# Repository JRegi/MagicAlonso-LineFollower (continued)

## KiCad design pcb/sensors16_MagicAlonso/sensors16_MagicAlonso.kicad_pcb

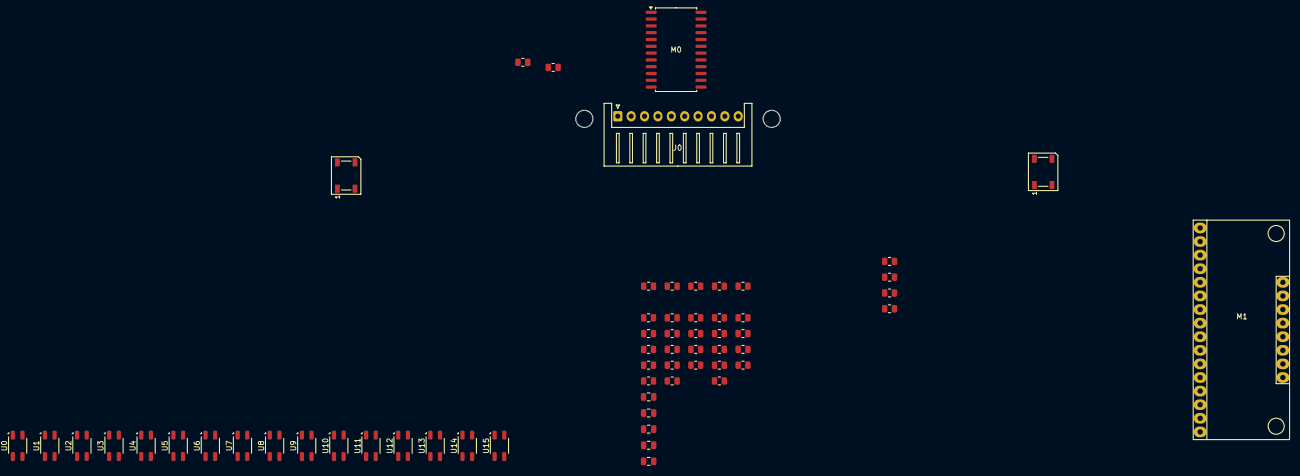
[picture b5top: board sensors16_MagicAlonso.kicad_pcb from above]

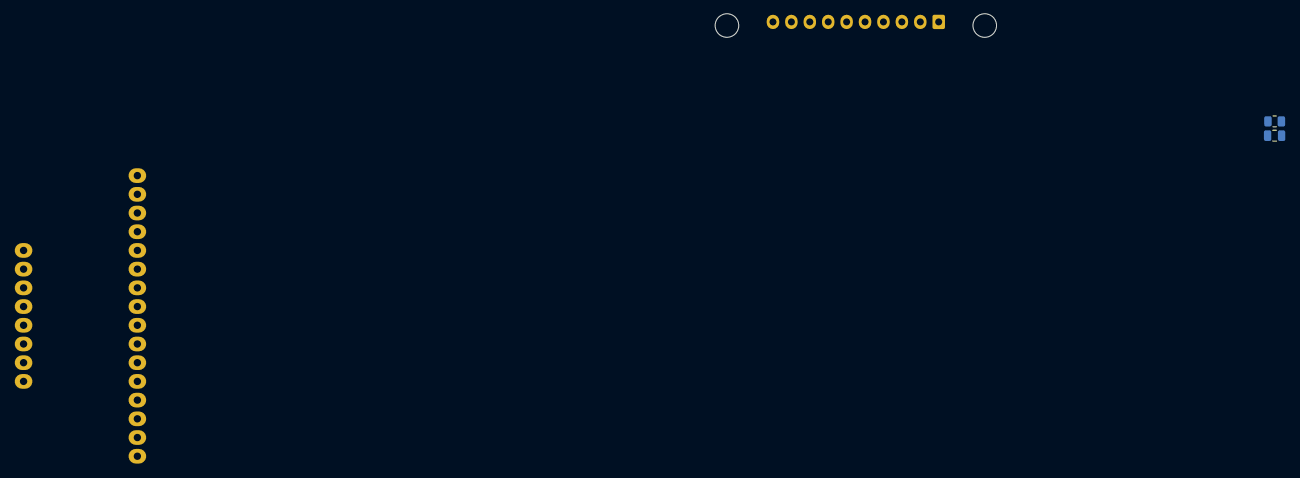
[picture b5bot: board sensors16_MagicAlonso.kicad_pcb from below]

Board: 2 copper layers, 64 parts (2 on the bottom side), 45 nets, no tracks yet.

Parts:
C0, C2, C3, C5: 100nF; C_0805_2012Metric
C1: 10uF; C_0805_2012Metric
C4: 22uF; C_0805_2012Metric
D0, D1: WS2812B; LED_WS2812B_PLCC4_5.0x5.0mm_P3.2mm
H1, H2: MountingHole; MountingHole_3.2mm_M3_DIN965
J0: Sensors; JST_XH_S10B-XH-A_1x10_P2.50mm_Horizontal
M0: CD74HC4067M; SOIC-24W_7.5x15.4mm_P1.27mm
M1: CD74HC4067; CD74HC4067_module
R0, R1, R2, R3, R8, R9, R10, R11, R16, R17, R18, R19, R25, R26, R27, R28, R33, R34: 100; R_0805_2012Metric
R4, R5, R6, R7, R12, R13, R14, R15, R20, R22, R23, R24, R29, R30, R31, R32: 20k; R_0805_2012Metric
R21: 10k; R_0805_2012Metric
U0, U1, U2, U3, U4, U5, U6, U7, U8, U9, U10, U11, U12, U13, U14, U15: QRE1113GR; OnSemi_CASE100CY

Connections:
+3.3V: C2.1, C4.1, J0.9, R33.2, R34.2
+3V3: C0.1, C1.1, M0.24 (VCC), M1.23 (VCC), R0.1, R1.1, R2.1, R3.1, R4.2, R5.2, R6.2, R7.2, R8.1, R9.1, R10.1, R11.1, R12.2, R13.2, R14.2, R15.2, R16.1, R17.1, R18.1, R19.1, R20.2, R22.2, R23.2, R24.2, R25.1, R26.1, R27.1, R28.1, R29.2, R30.2, R31.2, R32.2
/D_LED: D0.2 (DOUT), D1.4 (DIN)
/EN: M0.15 (~E), M1.22 (~EN), R21.1
/LEDs: D0.4 (DIN), J0.2
/QRE_0: M0.9 (I0), M1.16 (C0), R4.1, U0.3
/QRE_1: M0.8 (I1), M1.15 (C1), R5.1, U1.3
/QRE_2: M0.7 (I2), M1.14 (C2), R6.1, U2.3
/QRE_3: M0.6 (I3), M1.13 (C3), R7.1, U3.3
/QRE_4: M0.5 (I4), M1.12 (C4), R12.1, U4.3
/QRE_5: M0.4 (I5), M1.11 (C5), R13.1, U5.3
/QRE_6: M0.3 (I6), M1.10 (C6), R14.1, U6.3
/QRE_7: M0.2 (I7), M1.9 (C7), R15.1, U7.3
/QRE_8: M0.23 (I8), M1.8 (C8), R20.1, U8.3
/QRE_9: M0.22 (I9), M1.7 (C9), R22.1, U9.3
/QRE_10: M0.21 (I10), M1.6 (C10), R23.1, U10.3
/QRE_11: M0.20 (I11), M1.5 (C11), R24.1, U11.3
/QRE_12: M0.19 (I12), M1.4 (C12), R29.1, U12.3
/QRE_13: M0.18 (I13), M1.3 (C13), R30.1, U13.3
/QRE_14: M0.17 (I14), M1.2 (C14), R31.1, U14.3
/QRE_15: M0.16 (I15), M1.1 (C15), R32.1, U15.3
/S0: J0.7, M0.10 (S0), M1.21 (S0)
/S1: J0.6, M0.11 (S1), M1.20 (S1)
/S2: J0.5, M0.14 (S2), M1.19 (S2)
/S3: J0.4, M0.13 (S3), M1.18 (S3)
/SIG: J0.3, M0.1 (COM), M1.17 (SIG)
GND: C0.2, C1.2, C2.2, C3.2, C4.2, C5.2, D0.3 (VSS), D1.3 (VSS), J0.10, M0.12 (GND), M1.24 (GND), R21.2, U0.2 (K), U0.4, U1.2 (K), U1.4, U2.2 (K), U2.4, U3.2 (K), U3.4, U4.2 (K), U4.4, U5.2 (K), U5.4, U6.2 (K), U6.4, U7.2 (K), U7.4, U8.2 (K), U8.4, U9.2 (K), U9.4, U10.2 (K), U10.4, U11.2 (K), U11.4, U12.2 (K), U12.4, U13.2 (K), U13.4, U14.2 (K), U14.4, U15.2 (K), U15.4
unnamed: C3.1, D0.1 (VDD), R33.1
unnamed: C5.1, D1.1 (VDD), R34.1
unnamed: R0.2, U0.1 (A)
unnamed: R1.2, U1.1 (A)
unnamed: R2.2, U2.1 (A)
unnamed: R3.2, U3.1 (A)
unnamed: R8.2, U4.1 (A)
unnamed: R9.2, U5.1 (A)
unnamed: R10.2, U6.1 (A)
unnamed: R11.2, U7.1 (A)
unnamed: R16.2, U8.1 (A)
unnamed: R17.2, U9.1 (A)
unnamed: R18.2, U10.1 (A)
unnamed: R19.2, U11.1 (A)
unnamed: R25.2, U12.1 (A)
unnamed: R26.2, U13.1 (A)
unnamed: R27.2, U14.1 (A)
unnamed: R28.2, U15.1 (A)

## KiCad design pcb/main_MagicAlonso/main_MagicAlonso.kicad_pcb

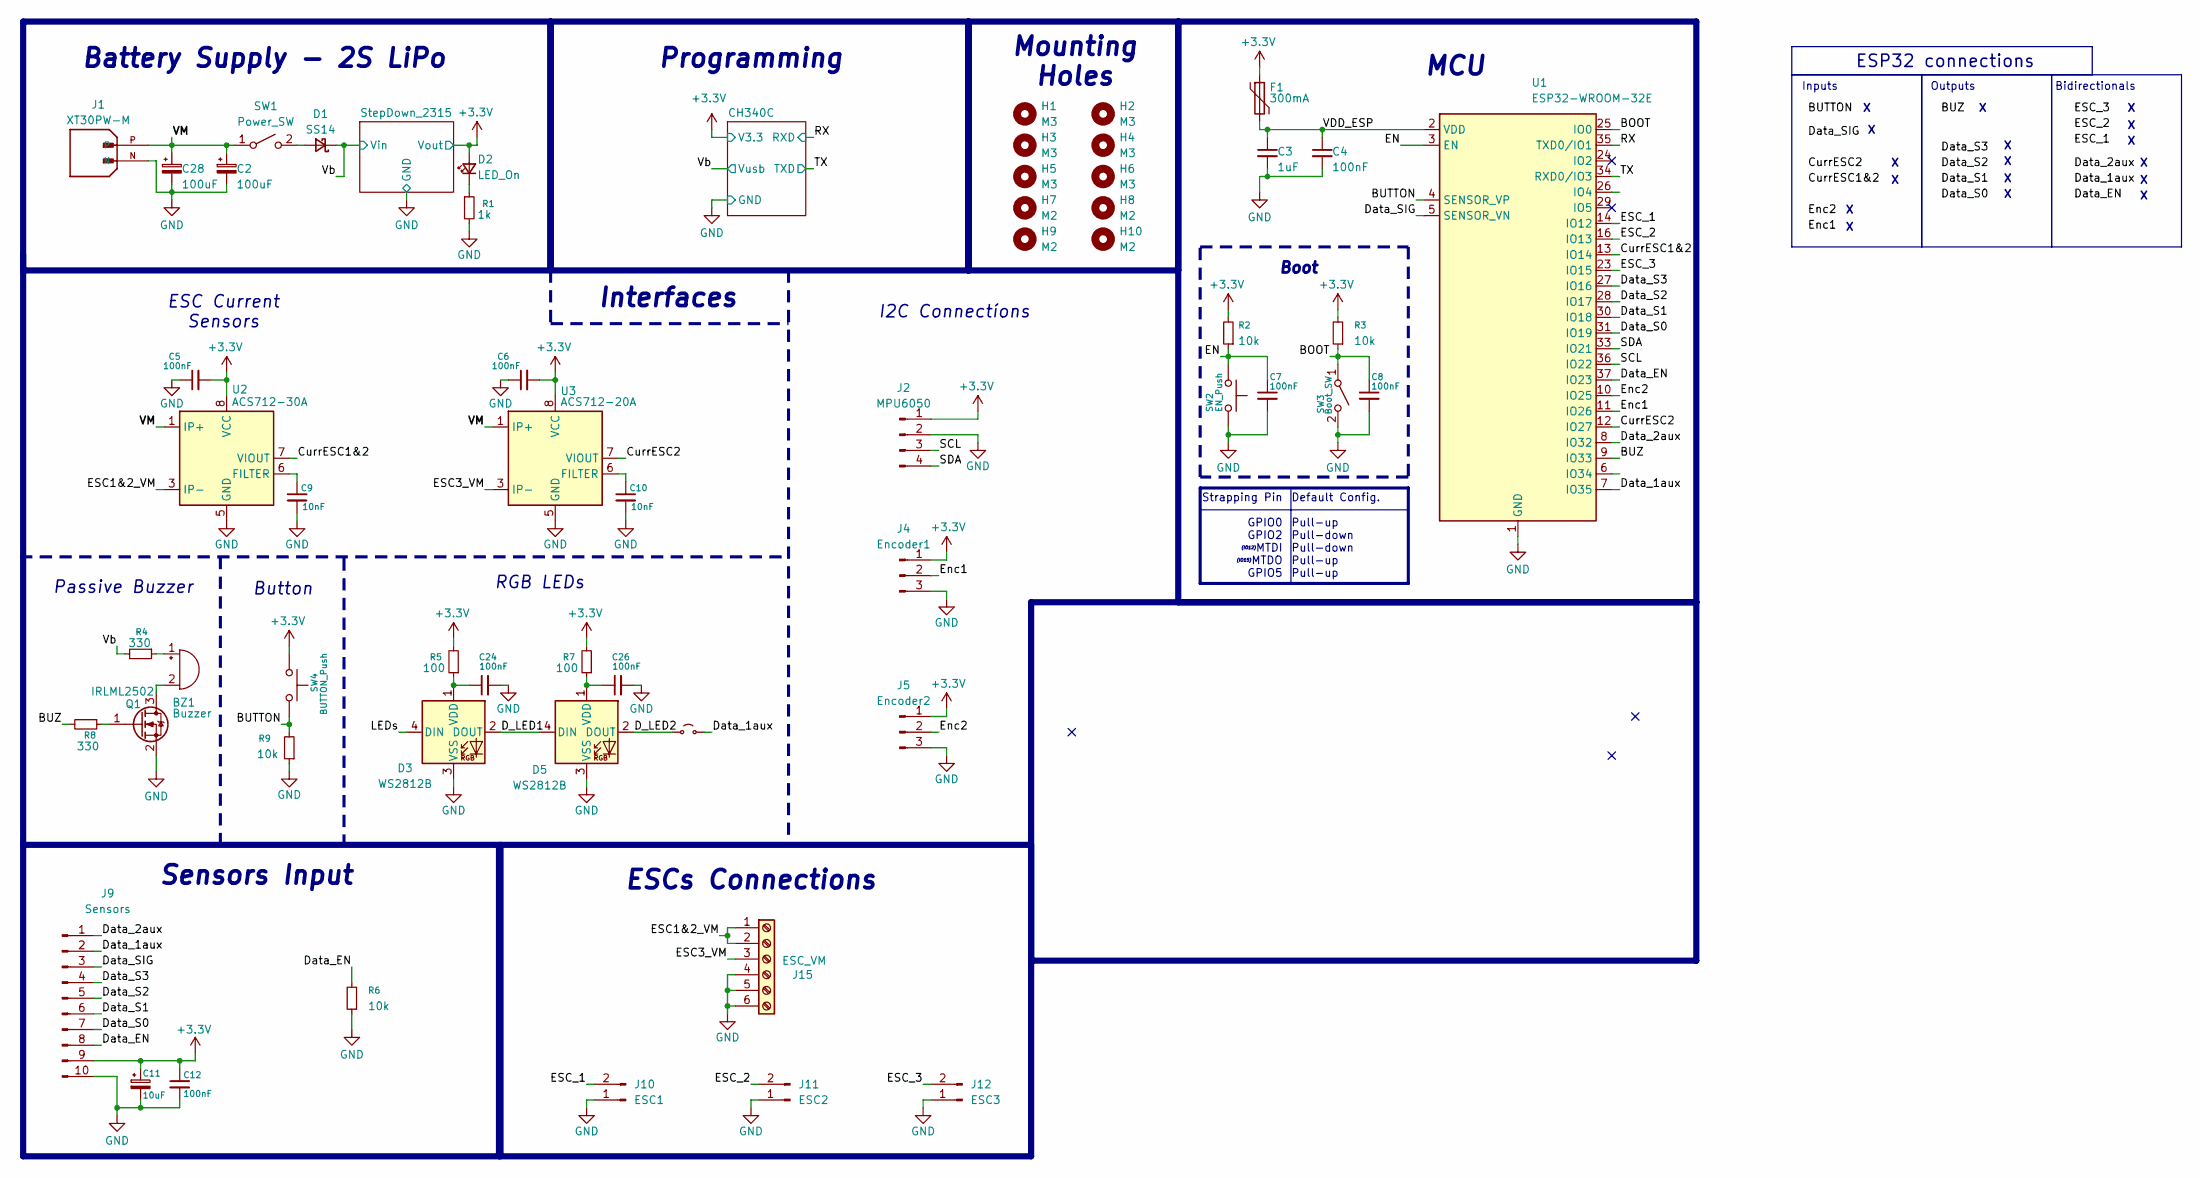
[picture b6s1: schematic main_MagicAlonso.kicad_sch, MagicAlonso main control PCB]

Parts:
BZ1: Buzzer; Buzzer_12x9.5RM7.6
C2, C28: 100uF; CP_Elec_6.3x5.4
C3: 1uF; C_0805_2012Metric
C4, C7, C12, C24, C26: 100nF; C_0805_2012Metric
C5, C6, C8: 100nF; C_0603_1608Metric
C9, C10: 10nF; C_0805_2012Metric
C11: 10uF; C_0805_2012Metric
D1: SS14; D_SMA
D2: LED_On; LED_0805_2012Metric
D3, D5: WS2812B; LED_WS2812B_PLCC4_5.0x5.0mm_P3.2mm
F1: 300mA; Fuse_1812_4532Metric_Pad1.30x3.40mm_HandSolder
H1, H2, H3, H4, H5, H6: M3; MountingHole_3mm
H7, H8, H9, H10: M2; MountingHole_2.2mm_M2
J1: XT30PW-M; AMASS_XT30PW-M; PARTREV 1.2
J2: MPU6050; MPU6050_Module
J4: Encoder1; JST_XH_B3B-XH-A_1x03_P2.50mm_Vertical
J5: Encoder2; JST_XH_B3B-XH-A_1x03_P2.50mm_Vertical
J9: Sensors; JST_XH_S10B-XH-A_1x10_P2.50mm_Horizontal
J10: ESC1; JST_XH_S2B-XH-A_1x02_P2.50mm_Horizontal
J11: ESC2; JST_XH_S2B-XH-A_1x02_P2.50mm_Horizontal
J12: ESC3; JST_XH_S2B-XH-A_1x02_P2.50mm_Horizontal
J15: ESC_VM; TerminalBlock_Phoenix_PT-1,5-6-3.5-H_1x06_P3.50mm_Horizontal
JP1: Jumper_2_Small_Open; R_1206_3216Metric
Q1: IRLML2502; SOT-23
R1: 1k; R_0603_1608Metric
R2, R3: 10k; R_0603_1608Metric
R4: 330; R_1206_3216Metric
R5, R7: 100; R_0805_2012Metric
R6, R9: 10k; R_0805_2012Metric
R8: 330; R_0805_2012Metric
SW1: Power_SW; SW_Slide-03_P2.54_L9_W4_H7
SW2: EN_Push; SW_SPST_CK_RS282G05A3
SW3: Boot_SW; SW_Slide-03_P2.54_L9_W4_H7
SW4: BUTTON_Push; SW_SPST_CK_RS282G05A3
U1: ESP32-WROOM-32E
U2: ACS712-30A; SOIC-8_3.9x4.9mm_P1.27mm
U3: ACS712-20A; SOIC-8_3.9x4.9mm_P1.27mm

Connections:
+3.3V: C5.2, C6.2, C11.1, C12.1, D2.2 (A), F1.1, J2.1, J4.1, J5.1, J9.9, R2.2, R3.2, R5.2, R7.2, SW4.1, U2.8 (VCC), U3.8 (VCC); also elsewhere on the board
/BOOT: C8.1, R3.1, SW3.1 (A), U1.25 (IO0)
/BUTTON: R9.2, SW4.2, U1.4 (SENSOR_VP)
/BUZ: R8.2, U1.9 (IO33)
/CurrESC1&2: U1.13 (IO14), U2.7 (VIOUT)
/CurrESC2: U1.12 (IO27), U3.7 (VIOUT)
/D_LED1: D3.2 (DOUT), D5.4 (DIN)
/D_LED2: D5.2 (DOUT), JP1.1 (A)
/Data_1aux: J9.2, JP1.2 (B), U1.7 (IO35)
/Data_2aux: J9.1, U1.8 (IO32)
/Data_EN: J9.8, R6.2, U1.37 (IO23)
/Data_S0: J9.7, U1.31 (IO19)
/Data_S1: J9.6, U1.30 (IO18)
/Data_S2: J9.5, U1.28 (IO17)
/Data_S3: J9.4, U1.27 (IO16)
/Data_SIG: J9.3, U1.5 (SENSOR_VN)
/EN: C7.1, R2.1, SW2.1, U1.3 (EN)
/ESC1&2_VM: J15.1, J15.2, U2.3 (IP-), U2.4 (IP-)
/ESC3_VM: J15.3, U3.3 (IP-), U3.4 (IP-)
/ESC_1: J10.2, U1.14 (IO12)
/ESC_2: J11.2, U1.16 (IO13)
/ESC_3: J12.2, U1.23 (IO15)
/Enc1: J4.2, U1.11 (IO26)
/Enc2: J5.2, U1.10 (IO25)
/LEDs: D3.4 (DIN)
/RX: U1.35 (TXD0/IO1); also elsewhere on the board
/SCL: J2.3, U1.36 (IO22)
/SDA: J2.4, U1.33 (IO21)
/TX: U1.34 (RXD0/IO3); also elsewhere on the board
/VDD_ESP: C3.1, C4.1, F1.2, U1.2 (VDD)
/VM: C2.1, C28.1, J1.P, SW1.1 (A), U2.1 (IP+), U2.2 (IP+), U3.1 (IP+), U3.2 (IP+)
/Vb: D1.1 (K), R4.2; also elsewhere on the board
GND: C2.2, C3.2, C4.2, C5.1, C6.1, C7.2, C8.2, C9.2, C10.2, C11.2, C12.2, C24.2, C26.2, C28.2, D3.3 (VSS), D5.3 (VSS), J1.N, J2.2, J4.3, J5.3, J9.10, J10.1, J11.1, J12.1, J15.4, J15.5, J15.6, Q1.2 (S), R1.2, R6.1, R9.1, SW2.2, SW3.2 (B), U1.1 (GND), U1.15 (GND), U1.38 (GND), U1.39 (GND), U2.5 (GND), U3.5 (GND); also elsewhere on the board
unnamed: BZ1.1 (+), R4.1
unnamed: BZ1.2 (-), Q1.3 (D)
unnamed: D1.2 (A), SW1.2 (B)
unnamed: D2.1 (K), R1.1
unnamed: C24.1, D3.1 (VDD), R5.1
unnamed: C26.1, D5.1 (VDD), R7.1
unnamed: Q1.1 (G), R8.1
unnamed: C9.1, U2.6 (FILTER)
unnamed: C10.1, U3.6 (FILTER)

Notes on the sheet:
ESC Current Sensors
Strapping Pin GPIO0 GPIO2 MTDI MTDO GPIO5
Inputs
(IO12)
Passive Buzzer
(IO15)
I2C Connectíons
Mounting Holes
ESP32 connections
Battery Supply - 2S LiPo
Sensors Input
MCU
ESCs Connections
Boot
RGB LEDs
Outputs
Button
Interfaces
Bidirectionals
Default Config. Pull-up Pull-down Pull-down Pull-up Pull-up
Programming

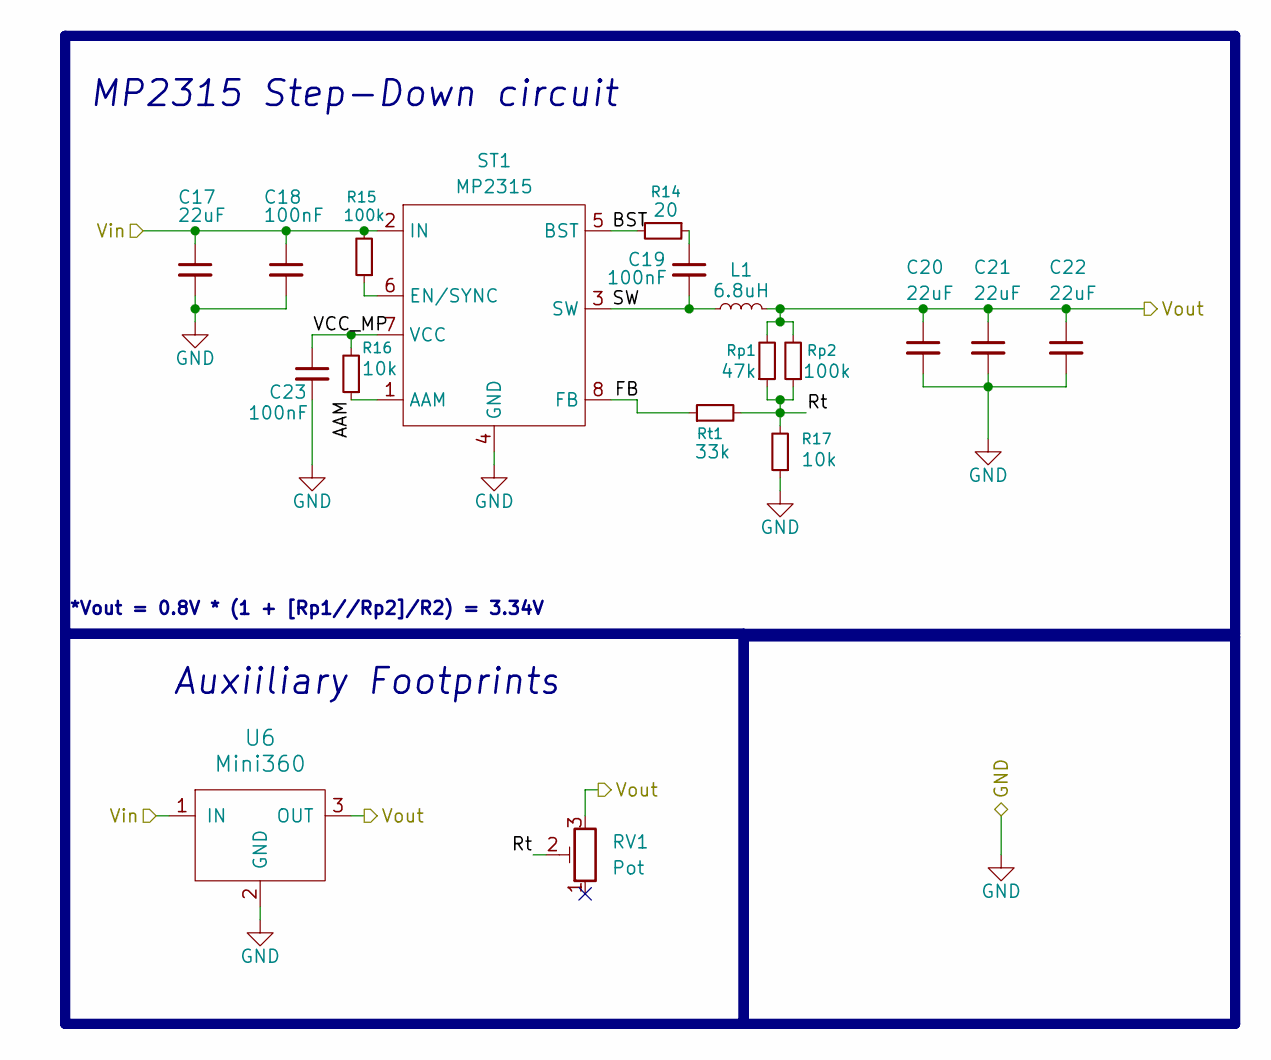
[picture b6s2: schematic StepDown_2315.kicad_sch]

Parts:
C17, C20, C21, C22: 22uF; C_0805_2012Metric
C18, C19, C23: 100nF; C_0603_1608Metric
L1: 6.8uH; L_TDK_SLF6025
R14: 20; R_0805_2012Metric
R15: 100k; R_0603_1608Metric
R16: 10k; R_0603_1608Metric
R17: 10k; R_0805_2012Metric
RV1: Pot; Potentiometer_Vishay_TS53YJ_Vertical
Rp1: 47k; R_0805_2012Metric
Rp2: 100k; R_0805_2012Metric
Rt1: 33k; R_0603_1608Metric
ST1: MP2315; TSOT-23-8
U6: Mini360; Mini360_step-down

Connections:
+3.3V: C20.1, C21.1, C22.1, L1.2, RV1.3, Rp1.2, Rp2.2, U6.3 (OUT); also elsewhere on the board
/StepDown_2315/AAM: R16.1, ST1.1 (AAM)
/StepDown_2315/BST: R14.2, ST1.5 (BST)
/StepDown_2315/FB: Rt1.1, ST1.8 (FB)
/StepDown_2315/Rt: R17.2, RV1.2, Rp1.1, Rp2.1, Rt1.2
/StepDown_2315/SW: C19.2, L1.1, ST1.3 (SW)
/StepDown_2315/VCC_SW: C23.1, R16.2, ST1.7 (VCC)
/Vb: C17.1, C18.1, R15.2, ST1.2 (IN), U6.1 (IN); also elsewhere on the board
GND: C17.2, C18.2, C20.2, C21.2, C22.2, C23.2, R17.1, ST1.4 (GND), U6.2 (GND); also elsewhere on the board
unnamed: C19.1, R14.1
unnamed: R15.1, ST1.6 (EN/SYNC)

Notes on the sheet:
*Vout = 0.8V * (1 + [Rp1//Rp2]/R2) = 3.34V
Auxiiliary Footprints
MP2315 Step-Down circuit

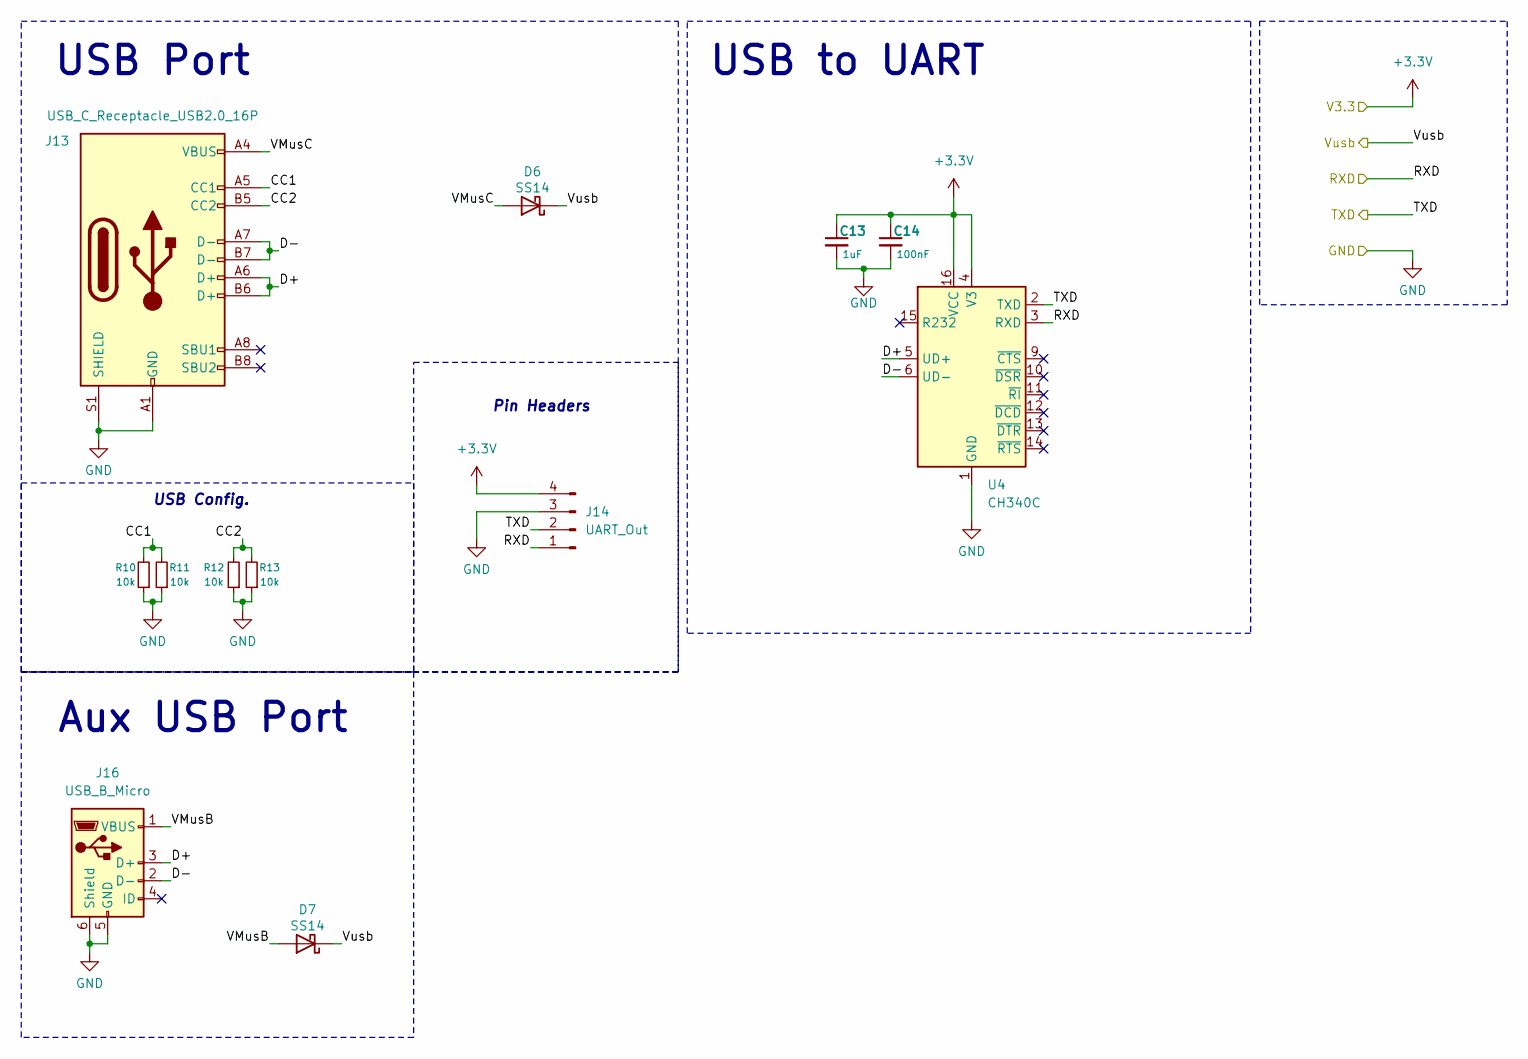
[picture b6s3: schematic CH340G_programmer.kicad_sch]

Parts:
C13: 1uF; C_0805_2012Metric
C14: 100nF; C_0603_1608Metric
D6, D7: SS14; D_SMA
J13: USB_C_Receptacle_USB2.0_16P; USB_C_Receptacle_GCT_USB4110
J14: UART_Out; JST_XH_S4B-XH-A_1x04_P2.50mm_Horizontal
J16: USB_B_Micro; USB_Micro-B_Amphenol_10104110_Horizontal
R10, R11, R12, R13: 10k; R_0603_1608Metric
U4: CH340C; SOIC-16_3.9x9.9mm_P1.27mm

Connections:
+3.3V: C13.1, C14.1, J14.4, U4.4 (V3), U4.16 (VCC); also elsewhere on the board
/CH340C/CC1: J13.A5 (CC1), R10.2, R11.2
/CH340C/CC2: J13.B5 (CC2), R12.2, R13.2
/CH340C/D+: J13.A6 (D+), J13.B6 (D+), J16.3 (D+), U4.5 (UD+)
/CH340C/D-: J13.A7 (D-), J13.B7 (D-), J16.2 (D-), U4.6 (UD-)
/CH340C/VMusB: D7.2 (A), J16.1 (VBUS)
/CH340C/VMusC: D6.2 (A), J13.A4 (VBUS), J13.A9 (VBUS), J13.B4 (VBUS), J13.B9 (VBUS)
/RX: J14.1, U4.3 (RXD); also elsewhere on the board
/TX: J14.2, U4.2 (TXD); also elsewhere on the board
/Vb: D6.1 (K), D7.1 (K); also elsewhere on the board
GND: C13.2, C14.2, J13.A1 (GND), J13.A12 (GND), J13.B1 (GND), J13.B12 (GND), J13.S1 (SHIELD), J14.3, J16.5 (GND), J16.6 (Shield), R10.1, R11.1, R12.1, R13.1, U4.1 (GND); also elsewhere on the board

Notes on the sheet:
USB to UART
Pin Headers
USB Config.
USB Port
Aux USB Port

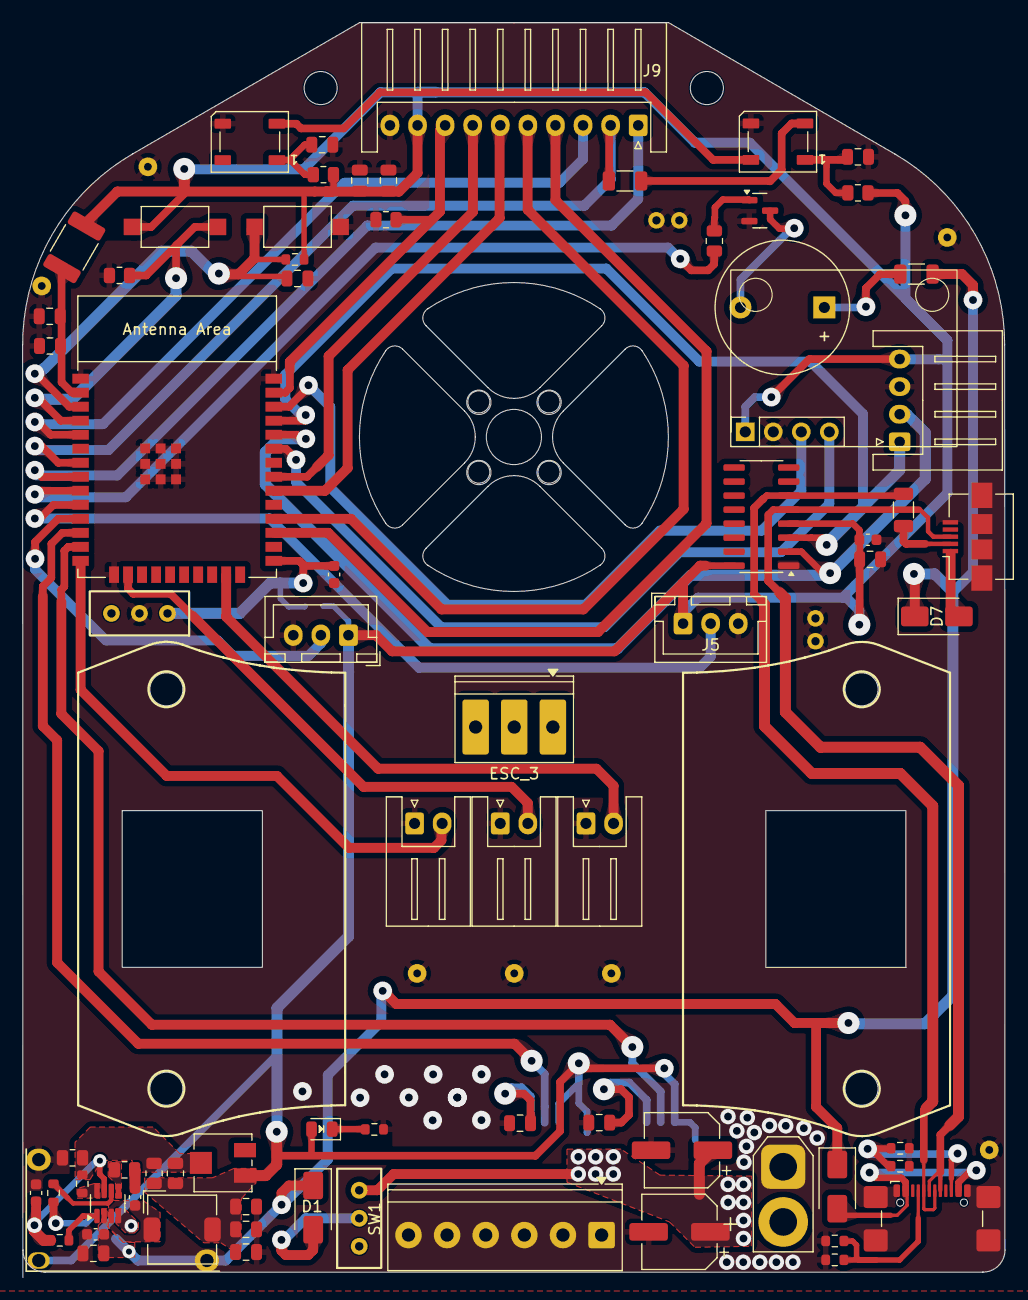
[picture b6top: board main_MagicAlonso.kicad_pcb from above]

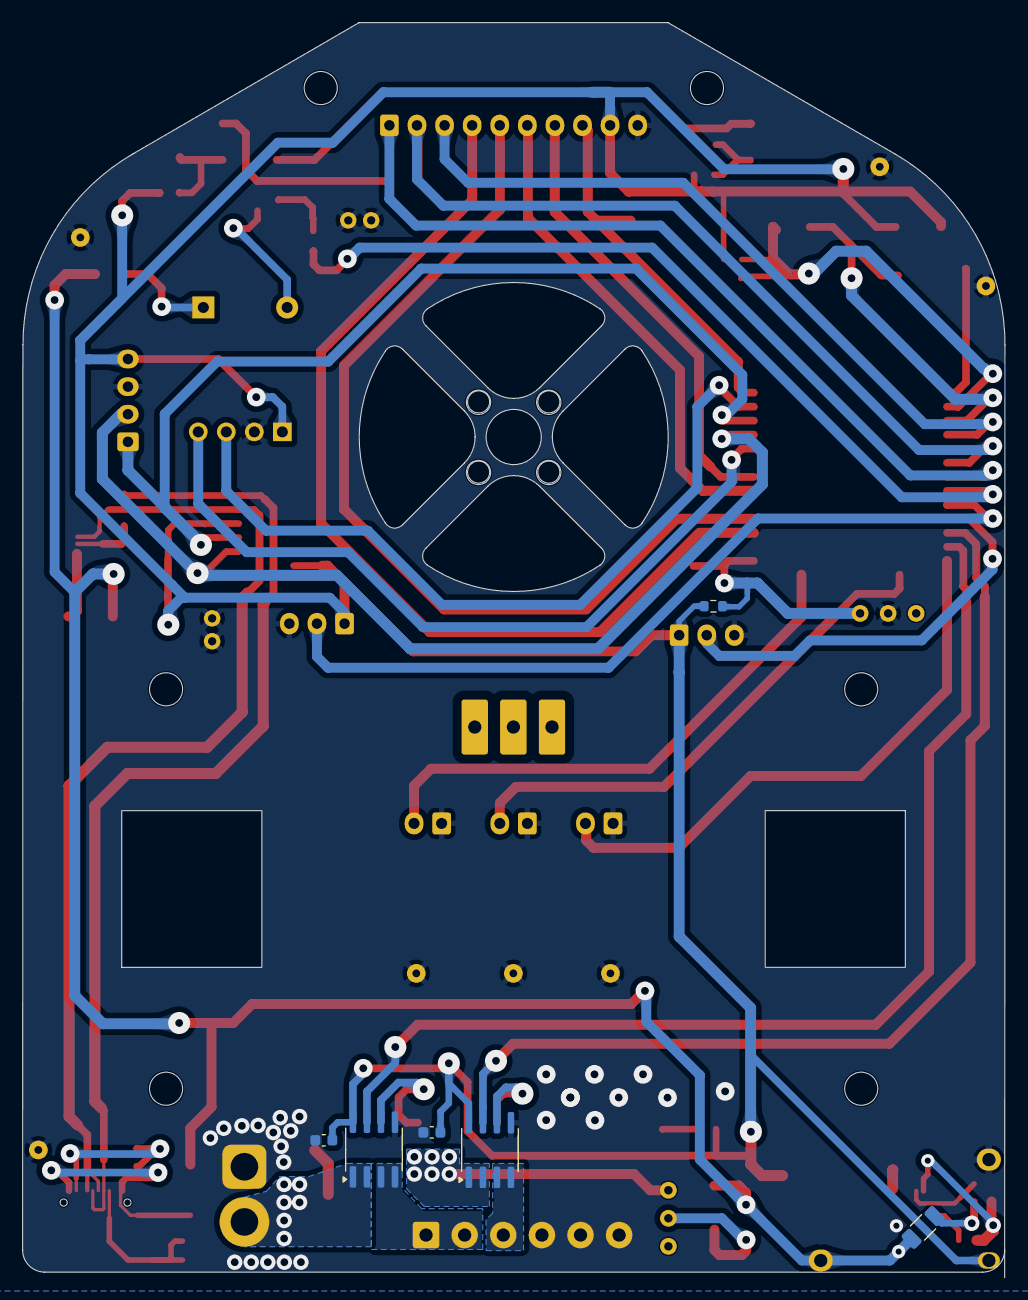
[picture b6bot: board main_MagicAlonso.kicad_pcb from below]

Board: 2 copper layers, 89.0 x 113.7 mm, 88 parts (5 on the bottom side), 55 nets.

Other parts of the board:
ESC_3: TerminalBlock_Phoenix_PT-1,5-3-3.5-H_1x03_P3.50mm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; TerminalBlock_Phoenix_PT-1,5-3-3.5-H_1x03_P3.50mm_Horizontal

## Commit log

2024-11-19 Adding libraries and main code
    Added a premature version of led controlling and array reading libraries as well with the base files for the main code.
2024-11-19 Changing term "Firmware" to "Software"
    Changed because of certain person being "hincha pelotas"
2024-11-19 Fixing minor mistakes
2024-12-02 Including basic main code and fixing a privacy problem in sensor_array.h
2025-04-04 2.9 to 1 transmission 3d files
2025-06-02 Kicad pcb intial drawing
2025-06-03 updated transmission module
2025-06-05 pcb schematic update
2025-06-06 Schematic & PCB updates
    made advancements on the schematic circuits and the PCB layout drawings.
2025-06-08 more schematic stuff
    Added ch340 and some more stuff
2025-06-09 more schematic
2025-06-09 yes, schematic
2025-06-10 hehe schematic go brr
2025-06-10 schematic go fiuuu
2025-06-10 esquematico
2025-06-14 StepDown schematic sub-file
    MP2315GJ circuit sub-file added.
2025-06-14 schematic and test commit
2025-06-16 Big changes PCB
    Advancements on the schematic were made:
    - Completed MP2315 circuit
    - Passive Buzzer
    - Mounting holes & other symbols added
    Also the PCB drawings were improved.
2025-06-17 Schematic and PCB
2025-06-17 schematic and pcb drawings
2025-06-18 schematic updates
2025-06-19 schematic almost finished
2025-06-20 some footprint assignment
2025-06-21 footprint assingment completed
2025-06-21 pcb footprint added
2025-06-23 pcb components & label fixes
2025-06-24 yes, pcb
2025-06-24 more pcb stuff ha
2025-06-25 pcb pcb
2025-06-25 pcb sync
2025-06-25 minor change
2025-06-28 pcb changes
2025-06-29 PCB components order
2025-06-30 PCB advancements
2025-07-01 mais avances en la pcb
2025-07-01 Update PCB
2025-07-05 misc
2025-07-06 first PCB layout done
2025-07-08 sensors pcb added
2025-07-08 sensors pcb update
2025-07-09 pcb update
2025-07-10 test project
2025-07-12 sensors16 pcb update
2025-07-22 Updated Motor_Mount 3d file
2025-07-28 pcbAAAAA
2025-07-30 simple main board added and donde
2025-08-06 Added main pcb image
2025-08-07 set simple pcb project as read-only
2025-08-07 line sensors body
2025-08-12 Photo added
2025-08-13 STM32 pcb created
2025-08-13 stm32 pcb schematic update
2025-08-15 bluepill pcb
2025-08-17 components arranged in bluepill pcb
2025-08-18 Routing of STM32F103 PCB done
2025-08-18 RGB led added to STM32 pcb
2025-08-18 printable_pcb added
2025-08-19 Minor pcb changes
2025-08-22 BluePill board archived
2025-08-25 platformio project added
2025-08-27 test de leds en main.c
2025-08-29 test de motores
2025-08-31 Adding an ESC control library
2025-08-31 reordered stl files
2025-08-31 PWM motor test
2025-09-01 reduccion V3 y rueda 26mm
2025-09-01 actualizacion Puente_V3
2025-09-02 qtr_array lib & main update: funciona loco
2025-09-02 image & README.md update
2025-09-02 updated image
2025-09-02 fixed README.md image embed
2025-09-03 Testeando PID básico
2025-09-04 Ultima version funcional del robot
    Tantas cosas que no sé qué poner
2025-09-07 Añadiendo libreria para el moduilo hc05
2025-09-07 Probando la lectura de sensores
    Se creó una nueva librería para la lectura de la regleta y se preparó un main para probar su funcionamiento mediante la devolución bluetooth de la posición.
2025-09-07 Actualizando platformio.ini
2025-09-07 Deshaciendose de operaciones con coma flotante
2025-09-08 Actualiza baudrate
2025-09-08 Simpplificando la librería de control de ESCs
2025-09-08 ch-ch-ch-chaaangeeeees
2025-09-08 no se
2025-09-09 DXF para reduccion 1404
2025-09-09 Proyecto main_Alonso_JLC creado
2025-09-10 Nueva libreria de QRE aun más simple
2025-09-10 anda lectura ponderada
2025-09-10 Añadiendo funcion de linea negra y linea blanca
2025-09-10 eeeeeeee
2025-09-10 delay_ms() via Systick
2025-09-10 Añadiendo funcion para leer canales individuales crudos
2025-09-10 añadiendo scan mode y promedio a qre_array
2025-09-10 Añadiendo calibracion y armado a la libreria esc
2025-09-10 Arreglos menores
    El parametro q de la funcion adc_set_regular_sequence ahora se convierte a uint8_t para que no salte un warning
2025-09-10 invirtiendo funciones de color de linea
2025-09-10 arreglando la libreria qre_array
2025-09-10 lord give me strength
2025-09-10 otra vez
2025-09-11 Revert "a"
    This reverts commit 75278b78612f6b1b08a58dba91497126b1027b74.
2025-09-11 Revert "otra vez"
    This reverts commit 1d58dda6d77afcfcf9c19ff143ab5fd3a12077ab.
2025-09-11 Revert "lord give me strength"
    This reverts commit a96218f59328659eba50ced5b14379ab15b0f1bc.
2025-09-11 Revert "arreglando la libreria qre_array"
    This reverts commit 10b3f97ac38eee443c69caae07baf9dcedc46cb5.
2025-09-11 Revert "Arreglos menores"
    This reverts commit 2d60d0db1a042bc01d9d06eb8f8fed894a2022b1.
2025-09-11 Revert "añadiendo scan mode y promedio a qre_array"
    This reverts commit 6eb4212f3370c194c844f441af7f3057af2f04e1.
2025-09-11 aver
2025-09-11 Implementando PID básico
2025-09-11 Intento de arreglar calibracion de ESC
2025-09-12 Añadiendo un delay más robusto
2025-09-12 Añadiendo libreria para comunicacion uart
2025-09-12 Añadiendo umbrales y funcion de perdida de linea
2025-09-12 buttons & rgb setup and basic functions
2025-09-12 no anda :) se queda bloqueado en calibracion
2025-09-12 ANDAA
2025-09-12 Revert "no anda :) se queda bloqueado en calibracion"
    This reverts commit 21bfcf9e1fdc6ba3f80ea4397a01b35184c8c22c.
2025-09-12 Revert "buttons & rgb setup and basic functions"
    This reverts commit 612e09d623bfe37c0d35b974dc8abad284af33e1.
2025-09-12 Revert "Añadiendo umbrales y funcion de perdida de linea"
    This reverts commit 87b926e43c02d9452ca1bf7a14947c152ae40c60.
2025-09-12 calobración PD
2025-09-12 anda fenomeno
2025-09-16 PD calibration
2025-09-17 jlc pcb schematic
2025-10-03 por las dudas commiteo
2025-10-03 aniadiendo libreria receptor ir
2025-10-03 aniadiendo libreria hc05
2025-10-03 Revert "aniadiendo libreria receptor ir"
    This reverts commit a8d4d85dfe0b0c7f4325f52ef97438d16eb6c6aa.
2025-10-03 Revert "a?"
    This reverts commit 87287d2488e1a8a126d39d4fecd8ddf44f345263.
2025-10-07 Revert "aniadiendo libreria hc05"
    This reverts commit 59fb48c8d3b3335d5c0f00903e15913b2ec83e68.
2025-10-07 Cambiando floats por ints
2025-10-10 Perfeccionando la librería de sensores
2025-10-19 Muchas cosas
    Se que debería haberlo dividido en varios commits, mala mía.
    - Se movio toda la gestión de clocks y timers fuera de main, a la nueva librería "clocks".
    - Se implementaron métodos de manejo del tiempo (delays, millis, micros, etc) a la nueva librería "timing".
    - Se movió todo el sistema de botones y leds a la nueva librería "ui" y se mejoró en algunos aspectos.
    - En general se mejoró el funcionamiento de todo lo que sea timing y clocks.
2025-10-21 Arreglando errores y mejorando portabilidad
    - Se eliminaron algunas redundancias y activación de pines y timers no utilizados.
    -La variable timclk_hz pasó a ser obtenida desde APB2 en lugar de ser hardcodeada para hacer la librería portable a otros microcontroladores con distinta frecuencia de clock.
    - Se añadió un sistema de manejo de errores en la función de prioridades de la librería "clocks" para hacer la librería portable a otras versiones de libopencm3/stm32 donde el simbolo a llamar puede 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
    - Se cambió el tiempo de debounce en el botón de inicio de carrera para evitar mejor las oscilaciones mecánicas.
2025-10-22 Loop de control ahora por interrupción de TIM2
2025-10-28 save changes
2025-10-28 change .gitignore
2025-10-28 Fixed readme
2025-10-28 changed image name
2025-10-28 fixed readme?
2025-10-28 fixedfixed Readme
2025-10-28 jpg image
2025-10-28 change gitignore again
2025-10-29 un par de cosas
2025-11-12 encoder pcb
2025-11-12 PID calibration & broken menu
2025-11-12 arreglados los botones
2025-11-13 minor changes
2025-11-18 ch ch ch changes
    turnnn and face the strange
2025-11-19 IR anda con Sony (40KHz)
2025-11-19 ONESHOT125 & PWM_HZ macros
2025-11-19 funciona
2025-11-29 Seleccion ONESHOT125, PWM y cambios al menu
